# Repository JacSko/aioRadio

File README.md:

# aioRadio

## Project description
aioRadio (all-in-one Radio) is the ESP32-based system designed for FM, DAB and Online radio reception. It is based on Silicon Labs Si4684 chipset capable 
of decoding analog and digital radio. System consist of:
- Main custom-designed PCB with antenna input and 3,5mm jack audio output,
- st7796 480x320 LCD
- Rotary encoder with integrated push button

## Key features
- FM and DAB radio support
- Station list
- Band scan

## Building
System is based on esp-idf framework and works under freeRTOS control.

### Preconditions:
- download esp-idf toolchain
- source export.sh
### Build target
- go into project root directory and run:
```
./build_app.sh
```

### Build unit tests 
- go into project root directory and run:
```
./build_ut.sh
```

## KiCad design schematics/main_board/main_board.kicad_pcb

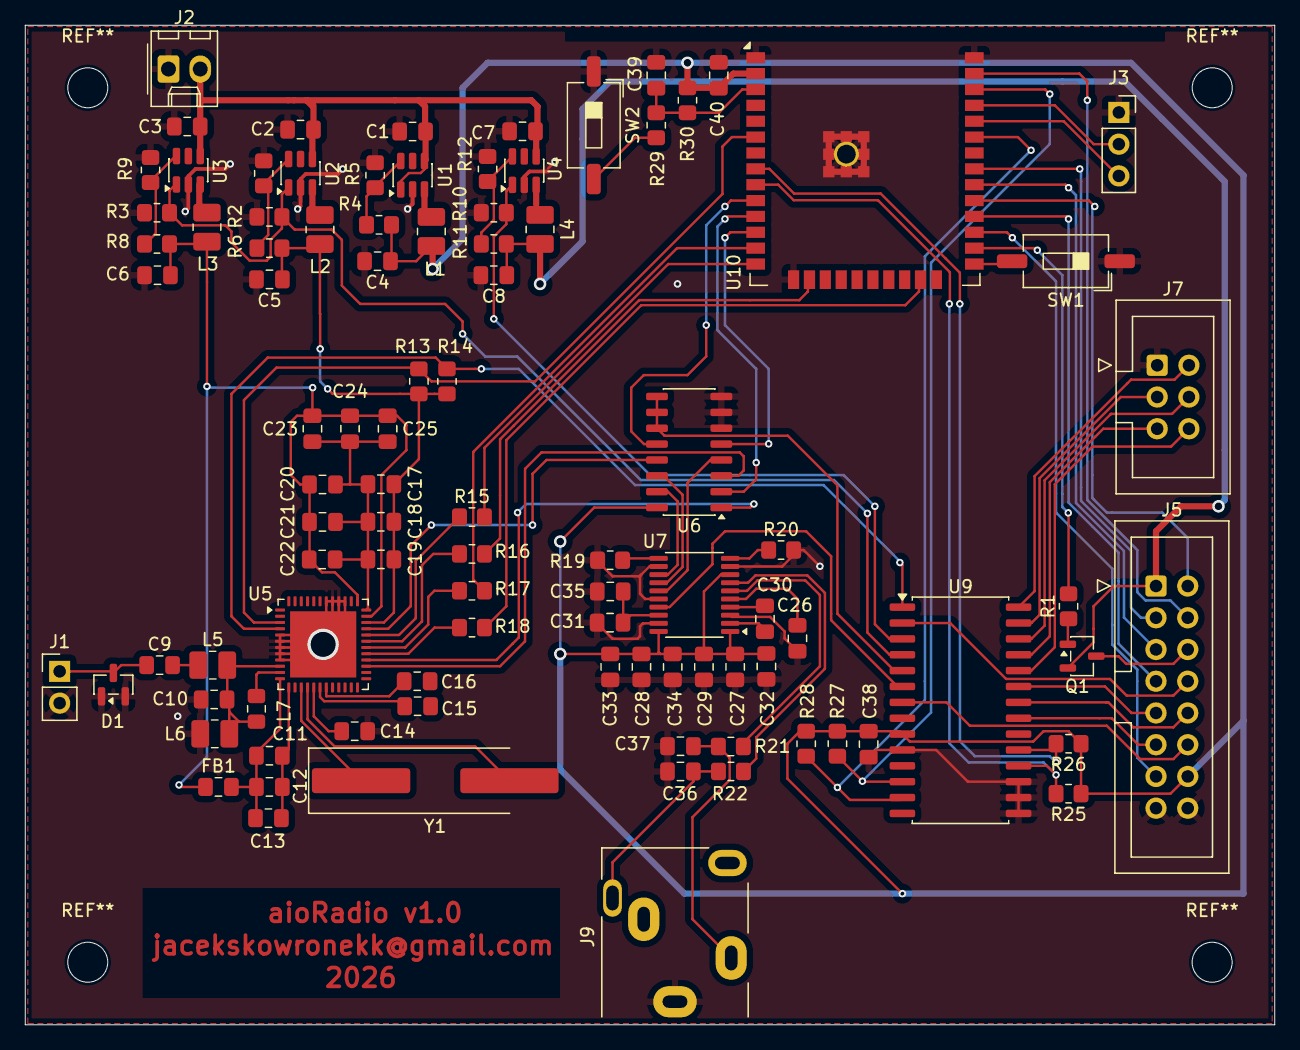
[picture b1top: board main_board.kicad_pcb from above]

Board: 2 copper layers, 100.0 x 80.0 mm, 96 parts (0 on the bottom side), 87 nets.

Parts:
C1, C2, C3, C7: 4.7uF; C_0805_2012Metric_Pad1.18x1.45mm_HandSolder
C4, C5, C6, C8: 10uF; C_0805_2012Metric_Pad1.18x1.45mm_HandSolder
C9: 33p; C_0805_2012Metric_Pad1.18x1.45mm_HandSolder
C10: 2,7pF; C_0805_2012Metric_Pad1.18x1.45mm_HandSolder
C11, C27, C28, C29, C31, C38, C40: 100n; C_0805_2012Metric_Pad1.18x1.45mm_HandSolder
C12, C18, C21, C24: 2,2pF; C_0805_2012Metric_Pad1.18x1.45mm_HandSolder
C13, C17, C20, C23: 8,2pF; C_0805_2012Metric_Pad1.18x1.45mm_HandSolder
C14, C15, C16, C19, C22, C25, C39: 1u; C_0805_2012Metric_Pad1.18x1.45mm_HandSolder
C26, C30: 2,2uF; C_0805_2012Metric_Pad1.18x1.45mm_HandSolder
C32, C33, C34, C35: 10u; C_0805_2012Metric_Pad1.18x1.45mm_HandSolder
C36, C37: 2.2n; C_0805_2012Metric_Pad1.18x1.45mm_HandSolder
D1: BAV99; SOT-23
FB1: 1k; C_0805_2012Metric_Pad1.18x1.45mm_HandSolder
J1: ANT; PinHeader_1x02_P2.54mm_Vertical
J2: VCC_INPUT_5V0; Molex_KK-254_AE-6410-02A_1x02_P2.54mm_Vertical
J3: UART; PinSocket_1x03_P2.54mm_Vertical
J5: CONTROL_BOARD; IDC-Header_2x08_P2.54mm_Vertical
J7: GPIO_EXT; IDC-Header_2x03_P2.54mm_Vertical
J9: LineOut; Jack_3.5mm_CUI_SJ1-3515N_Horizontal
L1, L2, L3, L4: 2.2uH; L_1008_2520Metric_Pad1.43x2.20mm_HandSolder
L5: 18nH; L_1008_2520Metric_Pad1.43x2.20mm_HandSolder
L6: 120nH; L_1008_2520Metric_Pad1.43x2.20mm_HandSolder
L7: 22nH; L_0805_2012Metric_Pad1.15x1.40mm_HandSolder
Q1: BC807; SOT-23-3
R1: 330R; R_0805_2012Metric_Pad1.20x1.40mm_HandSolder
R2, R3, R10, R13, R14, R25, R26, R27, R28, R30: 10k; R_0805_2012Metric_Pad1.20x1.40mm_HandSolder
R4, R6, R11: 464k; R_0805_2012Metric_Pad1.20x1.40mm_HandSolder
R5, R7, R9, R12: 100k; R_0805_2012Metric_Pad1.20x1.40mm_HandSolder
R8: 200k; R_0805_2012Metric_Pad1.20x1.40mm_HandSolder
R15, R16, R17, R18: 100; R_0805_2012Metric_Pad1.20x1.40mm_HandSolder
R19, R20, R29: 0; R_0805_2012Metric_Pad1.20x1.40mm_HandSolder
R21, R22: 470R; R_0805_2012Metric_Pad1.20x1.40mm_HandSolder
SW1: BOOT_MODE; SW_DIP_SPSTx01_Slide_6.7x4.1mm_W8.61mm_P2.54mm_LowProfile
SW2: RESET; SW_DIP_SPSTx01_Slide_6.7x4.1mm_W8.61mm_P2.54mm_LowProfile
U1, U2, U3, U4: TLV62569DDC; SOT-23-6
U5: SI4684 SMD; QFN-48-1EP_7x7mm_P0.5mm_EP5.3x5.3mm
U6: CD74HC5053; SO-16_3.9x9.9mm_P1.27mm
U7: PCM5102; TSSOP-20_4.4x6.5mm_P0.65mm
U9: MCP23017_SO; SOIC-28W_7.5x17.9mm_P1.27mm
U10: ESP32-WROOM-32E; ESP32-WROOM-32E_handsolder
Y1: Crystal; Crystal_SMD_HC49-SD_HandSoldering

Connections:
/Audio/DAC_MUTE: U7.17 (XSMT), U9.6 (GPB5)
/Audio/I2S_SOURCE_SEL: U6.9 (S3), U6.10 (S2), U6.11 (S1), U9.5 (GPB4)
/Audio/SOC_I2S_DCLK: U6.2 (B0), U10.11 (IO26)
/Audio/SOC_I2S_DFS: U6.5 (C0), U10.12 (IO27)
/Audio/SOC_I2S_DIN: U6.12 (A0), U10.10 (IO25)
/Audio/TUNER_I2S_DCLK: U5.28 (DSF), U6.1 (B1)
/Audio/TUNER_I2S_DFS: U5.27 (DCLK), U6.3 (C1)
/Audio/TUNER_I2S_DIN: U5.33 (DOUT), U6.13 (A1)
/Audio/VCC_3V3: C4.1, C27.1, C28.1, C29.1, C32.1, C33.1, C34.1, C38.1, C40.1, J5.14, L1.2, R4.1, R25.1, R26.1, R27.1, R28.1, R30.1, U6.16 (VDD), U7.1 (CPVDD), U7.8 (AVDD), U7.20 (DVDD), U9.9 (VDD), U10.2 (VDD)
/BTN: J5.9, U9.23 (GPA2)
/DATA_REG: J5.7, U10.28 (IO17)
/ENC_A: J5.10, U9.22 (GPA1)
/ENC_B: J5.11, U9.21 (GPA0)
/ENC_BNT: J5.12, U9.7 (GPB6)
/IR: J5.13, U10.27 (IO16)
/LED_PWM: J5.6, Q1.3 (C)
/PSU/PWR_DISPLAY_3V3: C8.1, J5.1, L4.2, Q1.2 (E), R11.1
/PSU/PWR_DISPLAY_EN: R10.1, U4.1 (EN), U9.3 (GPB2)
/PSU/PWR_TUNER_1V8: C6.1, C20.2, C21.2, C22.2, C23.2, C24.2, C25.2, FB1.1, L3.2, R8.1, U5.35 (VMEM), U5.37 (VCORE)
/PSU/PWR_TUNER_3V3: C5.1, C17.2, C18.2, C19.2, L2.2, R6.1, R13.1, R14.1, U5.34 (VIO)
/PSU/PWR_TUNER_EN: R2.1, R3.1, U2.1 (EN), U3.1 (EN), U9.4 (GPB3)
/PSU/VCC_INPUT_5V0: C1.1, C2.1, C3.1, C7.1, J2.2, U1.1 (EN), U1.4 (VIN), U2.4 (VIN), U3.4 (VIN), U4.4 (VIN)
/RESET: J5.8, U9.2 (GPB1)
/SOC/DISPLAY_LED_PWM: R1.2, U10.26 (IO4)
/SOC/EXP_I2C_SCK: R27.2, U9.12 (SCK), U10.36 (IO22)
/SOC/EXP_I2C_SDA: R28.2, U9.13 (SDA), U10.33 (IO21)
/SOC/EXP_i2C_INT: R26.2, U9.19 (INTB), U10.8 (IO32)
/SOC/EXP_i2C_RESET: R25.2, U9.18 (~RESET), U10.9 (IO33)
/SOC/SOC_BOOT: SW1.2, U10.25 (IO0)
/SOC/SOC_RESET: R29.2, SW2.2
/SOC/SOC_UART_RX: J3.3, U10.34 (RXD0/IO3)
/SOC/SOC_UART_TX: J3.2, U10.35 (TXD0/IO1)
/SPI_CLK: J5.5, U10.30 (IO18)
/SPI_CS: J5.2, U10.29 (IO5)
/SPI_MISO: J5.3, U10.31 (IO19)
/SPI_MOSI: J5.4, U10.37 (IO23)
/TUNER_CLK: R17.2, U10.13 (IO14)
/TUNER_CS: R18.2, U10.23 (IO15)
/TUNER_INT: R13.2, U5.3 (~INTB), U10.6 (IO34)
/TUNER_MISO: R15.2, U10.14 (IO12)
/TUNER_MOSI: R16.2, U10.16 (IO13)
/TUNER_RESET: R14.2, U5.4 (~RSTB), U9.1 (GPB0)
/Tuner/ANT_IN: C9.1, D1.3 (K), J1.1 (In)
GND: C1.2, C2.2, C3.2, C4.2, C5.2, C6.2, C7.2, C8.2, C10.2, C14.2, C26.2, C27.2, C28.2, C29.2, C31.2, C32.2, C33.2, C34.2, C35.2, C36.2, C37.2, C38.2, C39.2, C40.2, D1.1 (K), D1.2 (A), J1.2 (Ext), J2.1, J3.1, J5.15, J5.16, J7.1, J9.S, L6.2, R2.2, R3.2, R5.2, R7.2, R9.2, R10.2, R12.2, R19.1, R20.2, SW1.1, SW2.1, U1.2 (GND), U2.2 (GND), U3.2 (GND), U4.2 (GND), U5.5 (SMODE), U5.6 (RFREF), U5.7 (RFREF), U5.8 (RFREF), U5.9 (RFREF), U5.39 (GNDD), U5.40 (GNDD), U5.41 (GNDD), U5.42 (GNDD), U5.49 (GND), U6.6 (INH), U6.7 (VEE), U6.8 (VSS), U7.3 (CPGND), U7.9 (AGND), U7.12 (SCK), U7.16 (FMT), U7.19 (DGND), U9.10 (VSS), U9.15 (A0), U9.16 (A1), U9.17 (A2), U10.1 (GND), U10.15 (GND), U10.38 (GND), U10.39 (GND)
unnamed: C9.2, L5.1
unnamed: C36.1, J9.R, R22.1
unnamed: C37.1, J9.T, R21.2
unnamed: J7.2, U9.28 (GPA7)
unnamed: J7.3, U9.27 (GPA6)
unnamed: J7.4, U9.26 (GPA5)
unnamed: J7.5, U9.25 (GPA4)
unnamed: J7.6, U9.24 (GPA3)
unnamed: Q1.1 (B), R1.1
unnamed: R4.2, R5.1, U1.6 (FB)
unnamed: L1.1, U1.3 (SW)
unnamed: R6.2, R7.1, U2.6 (FB)
unnamed: L2.1, U2.3 (SW)
unnamed: R8.2, R9.1, U3.6 (FB)
unnamed: L3.1, U3.3 (SW)
unnamed: R11.2, R12.1, U4.6 (FB)
unnamed: L4.1, U4.3 (SW)
unnamed: C11.2, C12.2, C13.2, U5.13 (ABYP)
unnamed: C14.1, U5.17 (DACREF)
unnamed: C17.1, C18.1, C19.1, C20.1, C21.1, C22.1, C23.1, C24.1, C25.1, U5.36 (DBYP)
unnamed: C15.1, U5.18 (LOUT)
unnamed: R15.1, U5.32 (MISO)
unnamed: R16.1, U5.31 (MOSI)
unnamed: C16.1, U5.19 (ROUT)
unnamed: R17.1, U5.30 (SCLK)
unnamed: R18.1, U5.29 (SSB)
unnamed: C11.1, C12.1, C13.1, FB1.2, U5.12 (VA)
unnamed: C10.1, L5.2, L6.1, L7.1, U5.10 (VHFI)
unnamed: L7.2, U5.11 (VHFSW)
unnamed: U5.15 (XTALI), Y1.1
unnamed: U5.16 (XTALO), Y1.2
unnamed: U6.14 (A), U7.14 (DIN)
unnamed: U6.15 (B), U7.13 (BCK)
unnamed: U6.4 (C), U7.15 (LRCK)
unnamed: C30.2, U7.4 (CAPM)
unnamed: C30.1, U7.2 (CAPP)
unnamed: R20.1, U7.10 (DEMP)
unnamed: R19.2, U7.11 (FLT)
unnamed: C31.1, C35.1, U7.18 (LDOO)
unnamed: R21.1, U7.6 (OUTL)
unnamed: R22.2, U7.7 (OUTR)
unnamed: C26.1, U7.5 (VNEG)
unnamed: C39.1, R29.1, R30.2, U10.3 (EN)

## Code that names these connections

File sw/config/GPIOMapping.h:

#pragma once
#include "GPIODefs.h"

namespace drivers::gpio {
   enum class GPIO : uint16_t
   {
      ONBOARD_LED      = SOC_GPIO2,
      ONBOARD_BTN      = SOC_GPIO0,

      DISPLAY_LED_PWM  = SOC_GPIO4,
      DISPLAY_CS       = SOC_GPIO5,
      TUNER_MISO       = SOC_GPIO12,
      TUNER_MOSI       = SOC_GPIO13,
      TUNER_CLK        = SOC_GPIO14,
      TUNER_CS         = SOC_GPIO15,
      IR_IN            = SOC_GPIO16,
      DISPLAY_DATA_REG = SOC_GPIO17,
      DISPLAY_CLK      = SOC_GPIO18,
      DISPLAY_MISO     = SOC_GPIO19,
      GPIO_I2C_SDA     = SOC_GPIO21,
      GPIO_I2C_SCL     = SOC_GPIO22,
      DISPLAY_MOSI     = SOC_GPIO23,
      SOC_I2S_DOUT     = SOC_GPIO25,
      SOC_I2S_BCLK     = SOC_GPIO26,
      SOC_I2S_FS       = SOC_GPIO27,
      GPIO_I2C_INT     = SOC_GPIO32,
      GPIO_I2C_RESET   = SOC_GPIO33,
      TUNER_INT        = SOC_GPIO34,
      TUNER_RST        = I2C_GPIOB0,
      DISPLAY_RST      = I2C_GPIOB1,
      PWR_DISPLAY_EN   = I2C_GPIOB2,
      PWR_TUNER_EN     = I2C_GPIOB3,
      I2S_SOURCE_SEL   = I2C_GPIOB4,
      DAC_MUTE         = I2C_GPIOB5,
      CNT_ENC_BTN      = I2C_GPIOB6,
      CNT_ENC_B        = I2C_GPIOA0,
      CNT_ENC_A        = I2C_GPIOA1,
      CNT_BTN          = I2C_GPIOA2
   };
}
